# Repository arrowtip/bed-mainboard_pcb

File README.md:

# bed-mainboard_pcb

Simple PCB for using an ESP32 board to control Neopixel-LEDs based on audio-spectrum recorded by mircrophone.
Boards also includes interface for a rotary encoder and i2c devices.

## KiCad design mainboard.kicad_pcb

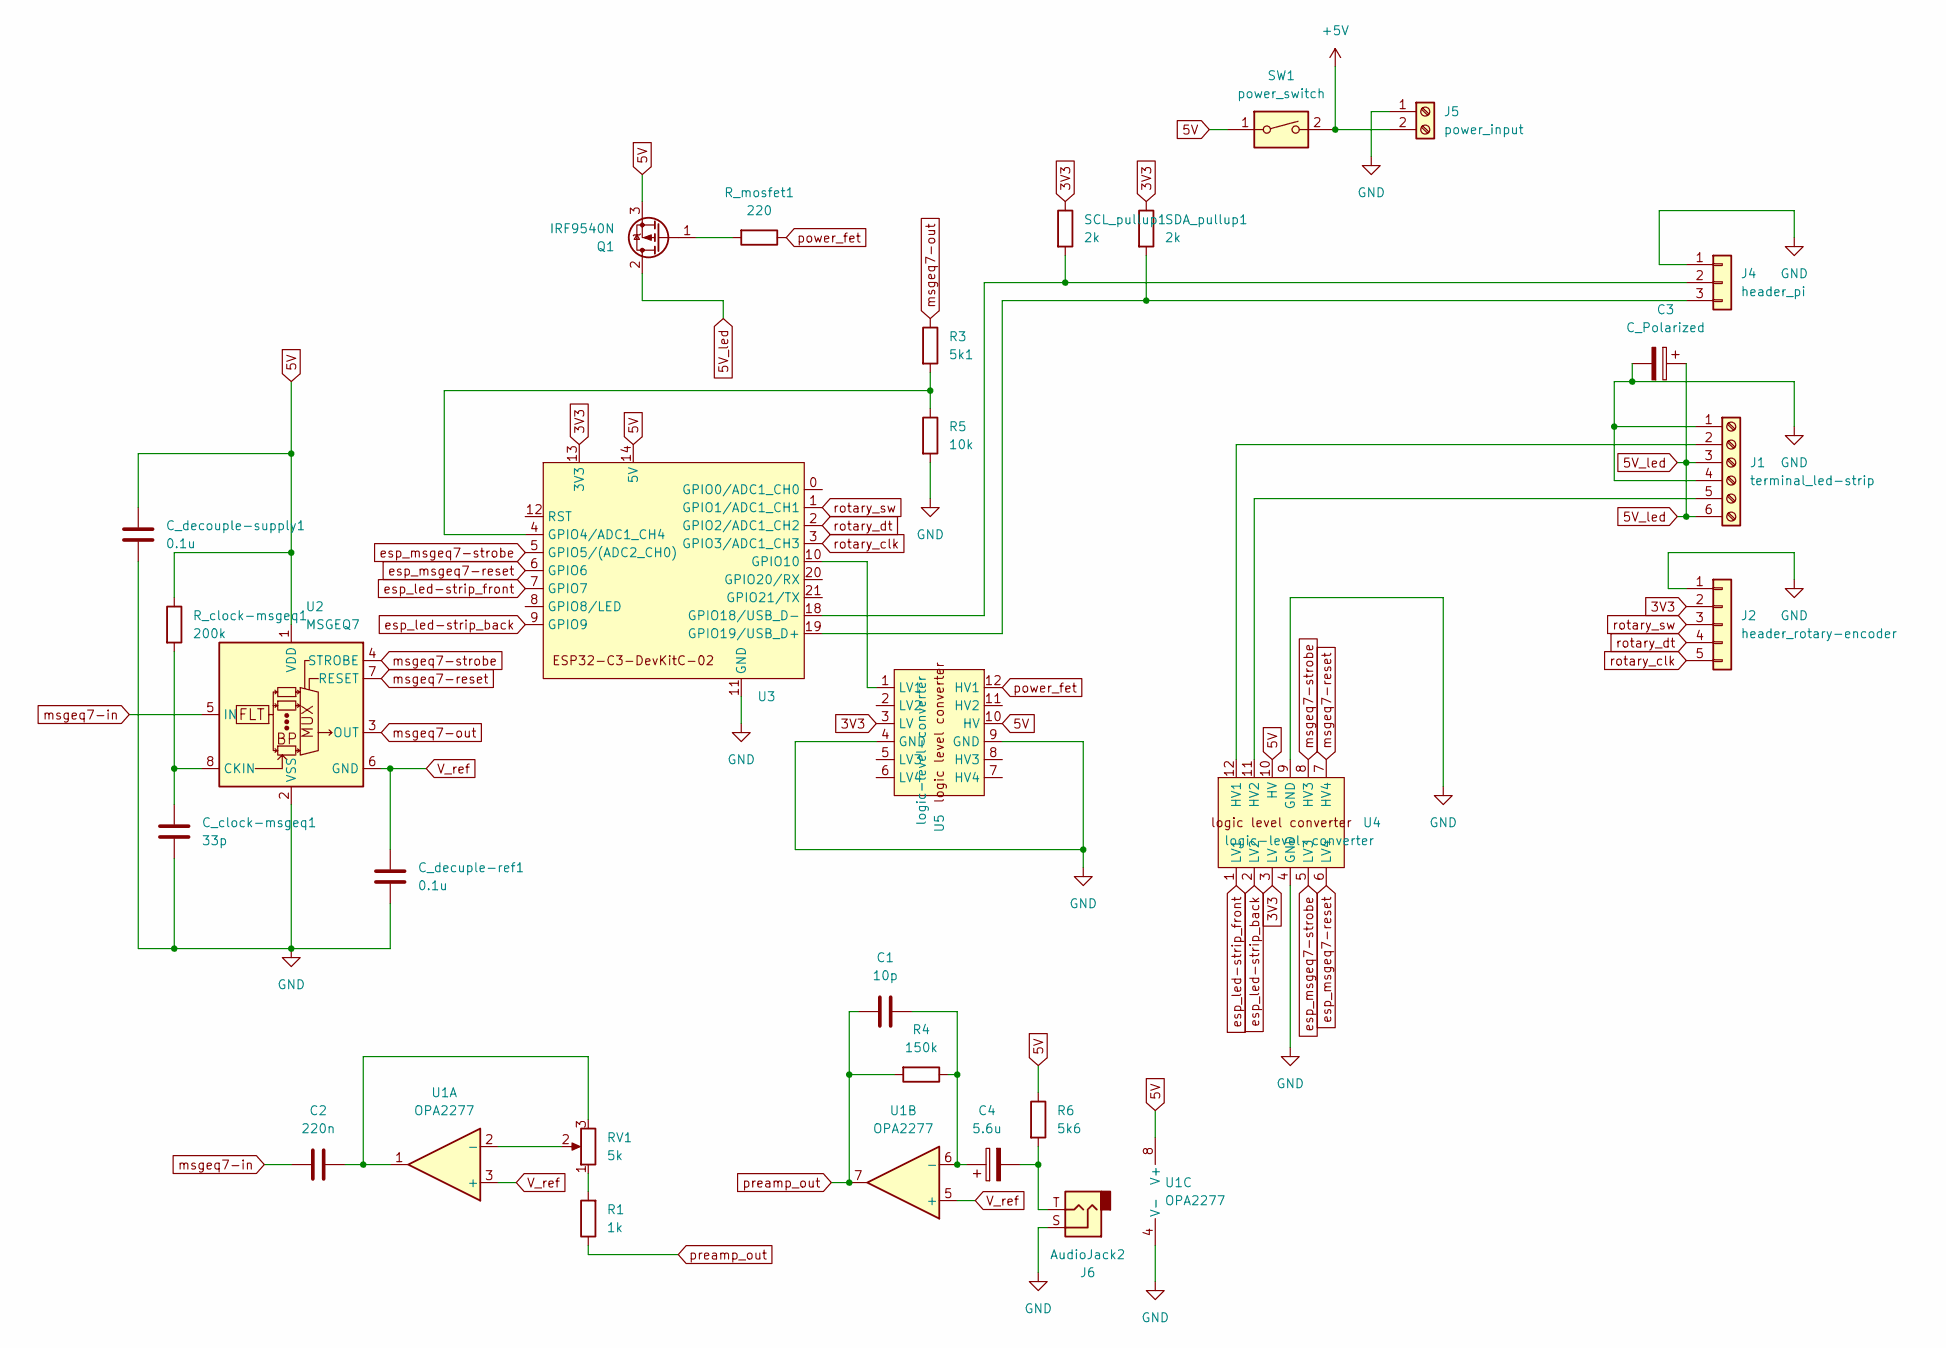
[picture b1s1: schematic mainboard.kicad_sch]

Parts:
C1: 10p; C_0603_1608Metric_Pad1.08x0.95mm_HandSolder; JLC 0603
C2: 220n; C_0805_2012Metric_Pad1.18x1.45mm_HandSolder; JLC 0805
C3: C_Polarized; CP_Radial_D8.0mm_P5.00mm
C4: 5.6u; CP_Radial_D5.0mm_P2.50mm; JLC 0805
C_clock-msgeq1: 33p; C_0603_1608Metric_Pad1.08x0.95mm_HandSolder; JLC 0603
C_decouple-supply1: 0.1u; C_0805_2012Metric_Pad1.18x1.45mm_HandSolder; JLC 0805
C_decuple-ref1: 0.1u; C_0805_2012Metric_Pad1.18x1.45mm_HandSolder; JLC 0805
J1: terminal_led-strip; ak3001_spring_wire_terminal_6x
J2: header_rotary-encoder; PinHeader_1x05_P2.54mm_Vertical
J4: header_pi; PinHeader_1x03_P2.54mm_Vertical
J5: power_input; ak3001_spring_wire_terminal_2x
J6: AudioJack2; jack_3.5mm_TS-only
Q1: IRF9540N; TO-220-3_Vertical
R1: 1k; R_0805_2012Metric_Pad1.20x1.40mm_HandSolder; JLC 0805
R3: 5k1; R_0805_2012Metric_Pad1.20x1.40mm_HandSolder; JLC 0805
R4: 150k; R_0805_2012Metric_Pad1.20x1.40mm_HandSolder; JLC 0805
R5: 10k; R_0805_2012Metric_Pad1.20x1.40mm_HandSolder; JLC 0805
R6: 5k6; R_0805_2012Metric_Pad1.20x1.40mm_HandSolder; JLC 0805
RV1: 5k; Potentiometer_Piher_PT-10-V10_Vertical
R_clock-msgeq1: 200k; R_0805_2012Metric_Pad1.20x1.40mm_HandSolder; JLC 0805
R_mosfet1: 220; R_0805_2012Metric_Pad1.20x1.40mm_HandSolder; JLC 0805
SCL_pullup1: 2k; R_0805_2012Metric_Pad1.20x1.40mm_HandSolder; JLC 0805
SDA_pullup1: 2k; R_0805_2012Metric_Pad1.20x1.40mm_HandSolder; JLC 0805
SW1: power_switch; ak3001_spring_wire_terminal_2x
U1: OPA2277; DIP-8_W7.62mm_Socket
U2: MSGEQ7; DIP-8_W7.62mm_Socket
U3: esp32_c3_dev-kit-c_02
U4, U5: logic-level-converter; sparkfun_logic_level_converter_bidirectional

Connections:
3V3: J2.2, SCL_pullup1.1, SDA_pullup1.1, U3.13 (3V3), U4.3 (LV), U5.3 (LV)
5V: C_decouple-supply1.1, Q1.3 (S), R6.1, R_clock-msgeq1.1, SW1.1, U1.8 (V+), U2.1 (VDD), U3.14 (5V), U4.10 (HV), U5.10 (HV)
5V_led: C3.1, J1.3, J1.6, Q1.2 (D)
+5V: J5.2, SW1.2
GND: C3.2, C_clock-msgeq1.2, C_decouple-supply1.2, C_decuple-ref1.2, J1.1, J1.4, J2.1, J4.1, J5.1, J6.S, R5.2, U1.4 (V-), U2.2 (VSS), U3.11 (GND), U4.4 (GND), U4.9 (GND), U5.4 (GND), U5.9 (GND)
unnamed: C2.2, RV1.3, U1.1
unnamed: C4.2, J6.T, R6.2
unnamed: J1.2, U4.12 (HV1)
unnamed: J1.5, U4.11 (HV2)
unnamed: J4.2, SCL_pullup1.2, U3.18 (GPIO18/USB_D-)
unnamed: J4.3, SDA_pullup1.2, U3.19 (GPIO19/USB_D+)
unnamed: Q1.1 (G), R_mosfet1.2
unnamed: R1.2, RV1.1
unnamed: RV1.2, U1.2 (-)
unnamed: C1.2, C4.1, R4.1, U1.6 (-)
unnamed: C_clock-msgeq1.1, R_clock-msgeq1.2, U2.8 (CKIN)
unnamed: R3.2, R5.1, U3.4 (GPIO4/ADC1_CH4)
unnamed: U3.10 (GPIO10), U5.1 (LV1)
V_ref: C_decuple-ref1.1, U1.3 (+), U1.5 (+), U2.6 (GND)
esp_led-strip_back: U3.9 (GPIO9), U4.2 (LV2)
esp_led-strip_front: U3.7 (GPIO7), U4.1 (LV1)
esp_msgeq7-reset: U3.6 (GPIO6), U4.6 (LV4)
esp_msgeq7-strobe: U3.5 (GPIO5/(ADC2_CH0)), U4.5 (LV3)
msgeq7-in: C2.1, U2.5 (IN)
msgeq7-out: R3.1, U2.3 (OUT)
msgeq7-reset: U2.7 (RESET), U4.7 (HV4)
msgeq7-strobe: U2.4 (STROBE), U4.8 (HV3)
power_fet: R_mosfet1.1, U5.12 (HV1)
preamp_out: C1.1, R1.1, R4.2, U1.7
rotary_clk: J2.5, U3.3 (GPIO3/ADC1_CH3)
rotary_dt: J2.4, U3.2 (GPIO2/ADC1_CH2)
rotary_sw: J2.3, U3.1 (GPIO1/ADC1_CH1)

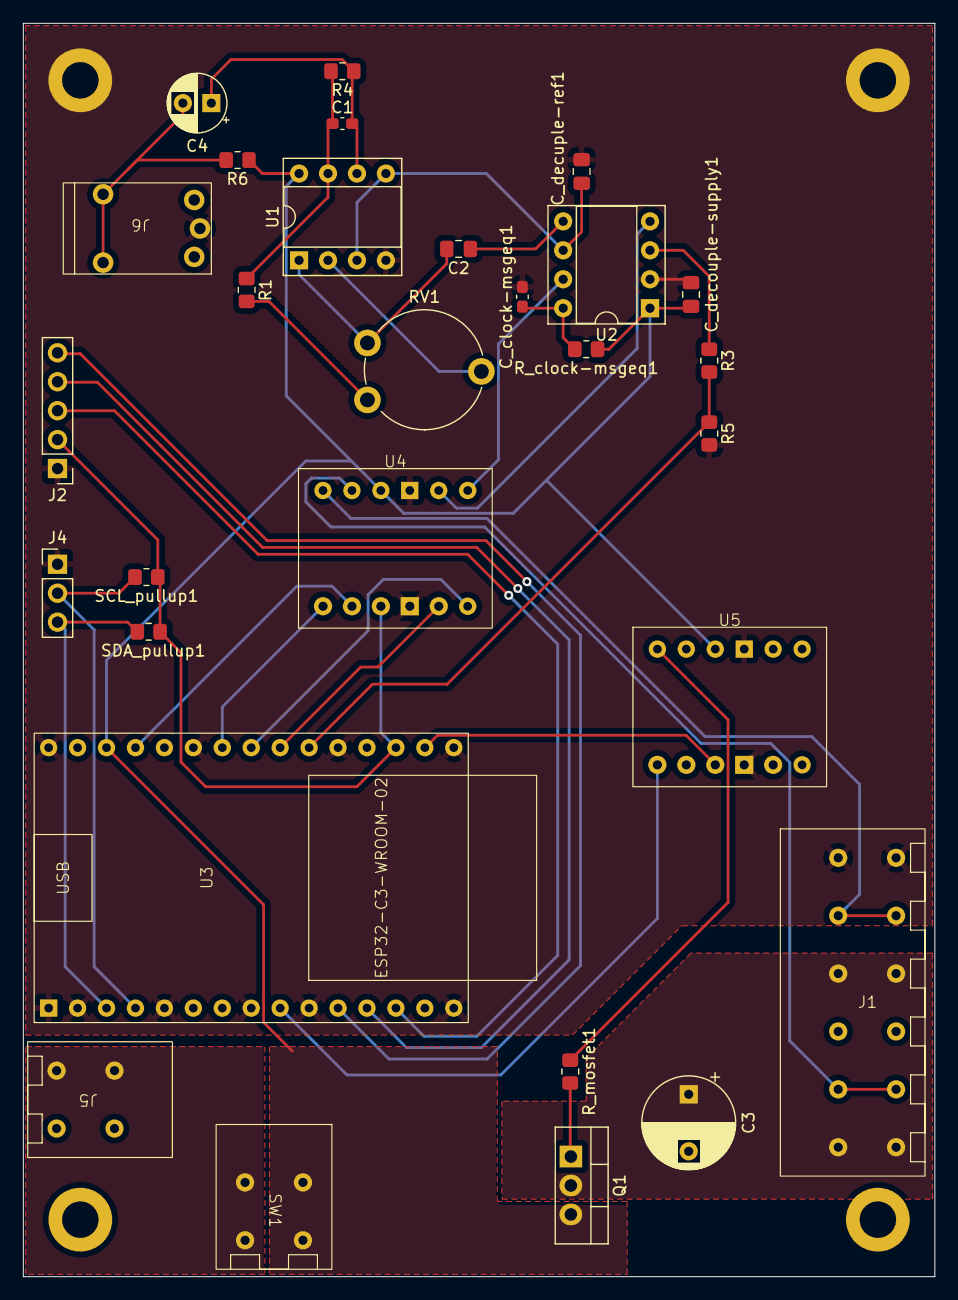
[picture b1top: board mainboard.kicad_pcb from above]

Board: 2 copper layers, 80.0 x 110.0 mm, 29 parts (0 on the bottom side), 32 nets.

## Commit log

2023-09-30 init git repo
2023-10-11 finish schematic
2023-10-12 move i2c pins
2023-10-12 add loudness control
2023-10-13 add referece voltage to opamps
2023-10-13 add fields for JLC manufacturing
2023-10-16 start routing tracks
2023-10-17 route tracks and add mounting holes
2023-10-17 add jlc part ids
2023-10-18 flip rotary encoder connector
2023-10-18 add proper values for voltage divider of msgeq7-out
2023-10-18 ground mounting holes
2023-10-26 add license
2023-10-26 add readme
